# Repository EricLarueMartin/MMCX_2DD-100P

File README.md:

# MMCX_2DD-100P
Adapter between MMCX connectors to a 2DD 100 pin connector for Gretina cards

Requires two PCBs on 47 mil board, one for even channel and one for odd channels.
MMCX_2DD-100P_Even.zip and MMCX_2DD-100P_Odd.zip

Uses MMCX connectors: MOLEX 0734150961

The other connector is a double density 100 pin DSub connector: ITT Cannon 2DD-100PF0

The pins for the connector are 031-9540-015

Any MMCX plug can connector to the adapter, such as MOLEX 0734150970

The connector housing is in three pieces, two half shells and a spacer that goes between them. 
The two half shells are made of two material so that channel labels and the UNC logo are visible. This is all contained in: HousingLogoLabeled.2mf

The boards will be mounted at and angle, and the pins need to be soldered on first. A jig is recommended to insert the board without bending the pins:
InsertionGuideA.stl and InsertionGuideB.stl

To solder the pins in the correct position a connector with the holes drilled so the pins don't get stuck was used previously. Printing a jig for the pins from 2DD-100P.ipt should also work, but verify the hole spacing first as I think it was slightly off.

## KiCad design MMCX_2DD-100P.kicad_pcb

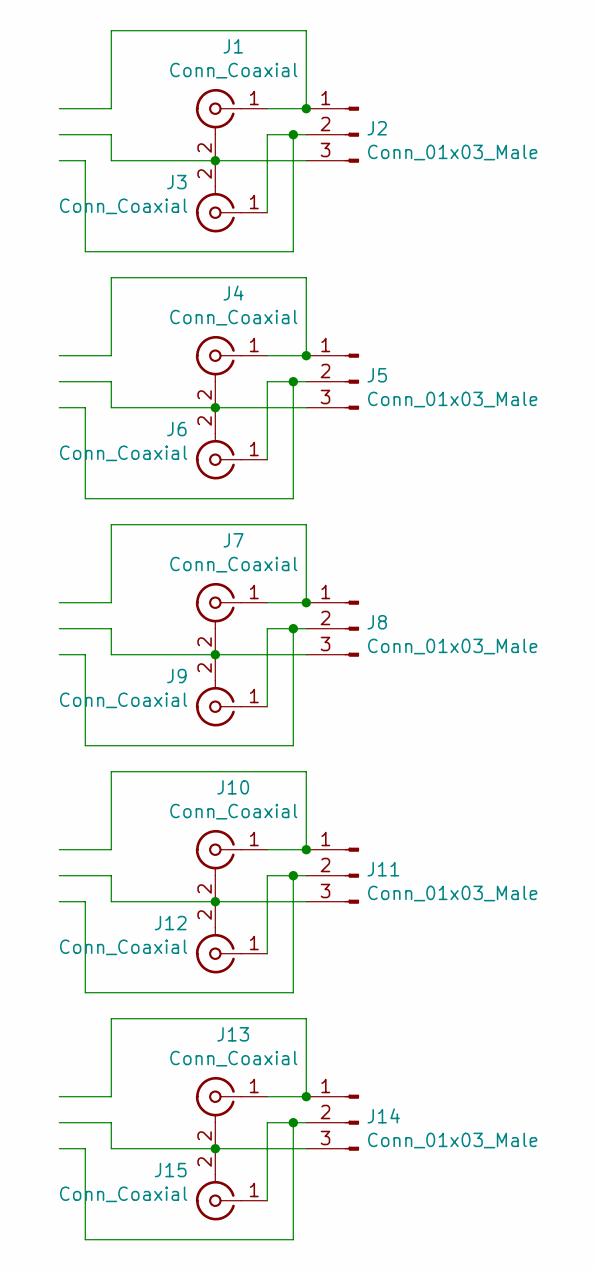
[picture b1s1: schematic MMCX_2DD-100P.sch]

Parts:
J1, J3, J4, J6, J7, J9, J10, J12, J13, J15: Conn_Coaxial; MMCX_EndLaunch_20mil_50ohm
J2, J5, J8, J11, J14: Conn_01x03_Male; 2xCoax_to_2DD

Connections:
unnamed: J1.1 (In), J2.1
unnamed: J1.2 (Ext), J2.3, J3.2 (Ext)
unnamed: J2.2, J3.1 (In)
unnamed: J4.1 (In), J5.1
unnamed: J4.2 (Ext), J5.3, J6.2 (Ext)
unnamed: J5.2, J6.1 (In)
unnamed: J7.1 (In), J8.1
unnamed: J7.2 (Ext), J8.3, J9.2 (Ext)
unnamed: J8.2, J9.1 (In)
unnamed: J10.1 (In), J11.1
unnamed: J10.2 (Ext), J11.3, J12.2 (Ext)
unnamed: J11.2, J12.1 (In)
unnamed: J13.1 (In), J14.1
unnamed: J13.2 (Ext), J14.3, J15.2 (Ext)
unnamed: J14.2, J15.1 (In)

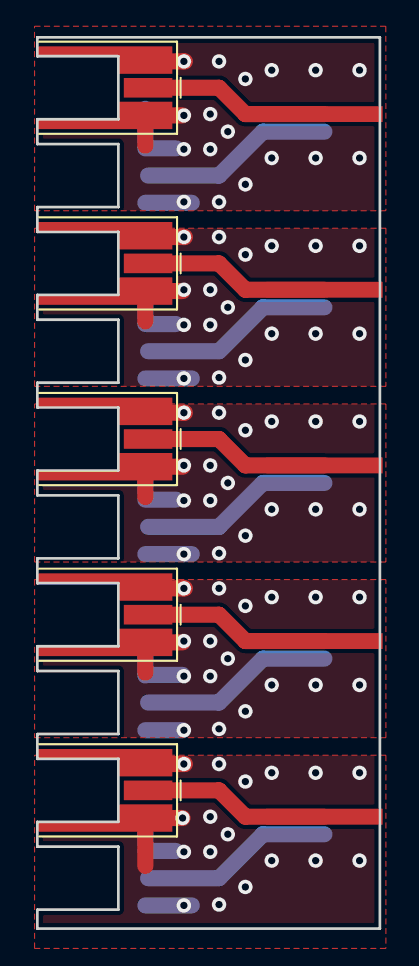
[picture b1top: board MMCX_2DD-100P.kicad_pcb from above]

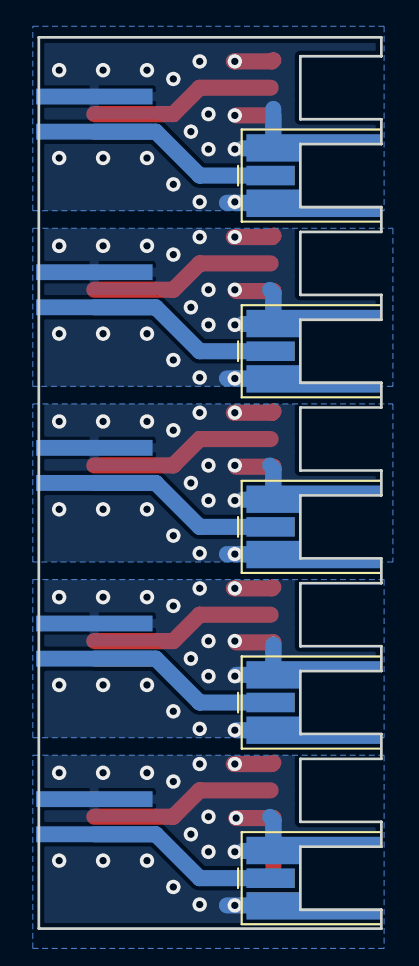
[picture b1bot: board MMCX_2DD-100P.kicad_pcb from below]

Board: 2 copper layers, 19.0 x 49.5 mm, 15 parts (10 on the bottom side), 15 nets.
